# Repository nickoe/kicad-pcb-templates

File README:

This is just some random PCB templates for Kicad.

RasPi-BplusHAT.kicad_pcb is imported from an Eagle pcb and fixed.
Taken from
http://www.raspberrypi.org/forums/viewtopic.php?f=100&t=82618

RasPi-BplusHAT-directimport.kicad_pcb is just the board saved directly
after importing it in Kicad.

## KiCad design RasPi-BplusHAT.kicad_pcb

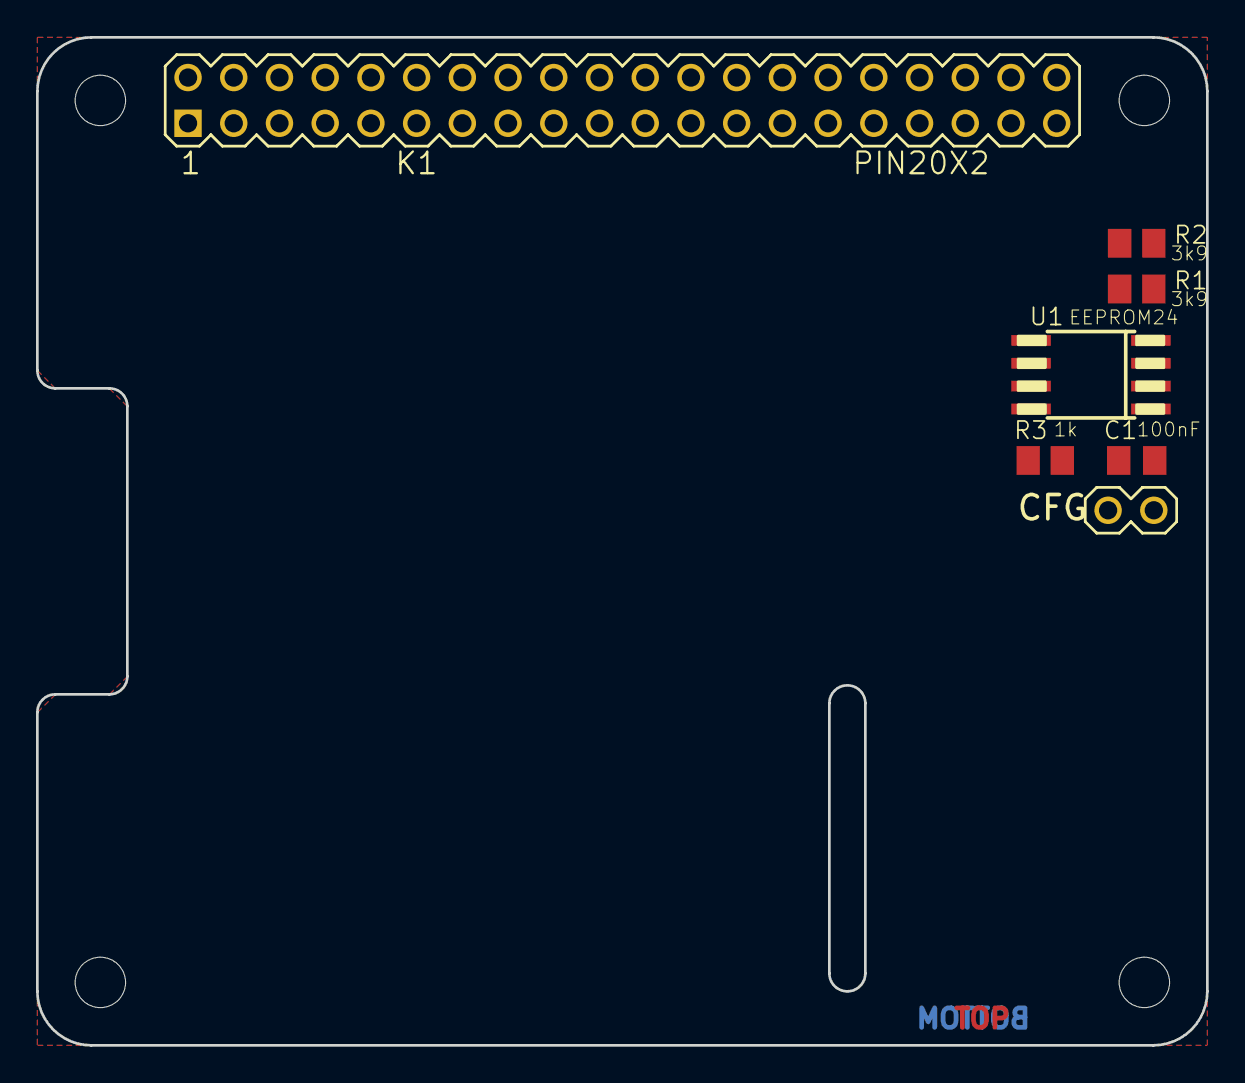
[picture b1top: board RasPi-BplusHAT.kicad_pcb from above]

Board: 2 copper layers, 65.0 x 56.0 mm, 11 parts (0 on the bottom side), 6 nets, no tracks yet.

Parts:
@HOLE0, @HOLE1, @HOLE2, @HOLE3: (no value)
C1: 100nF; C0805K
CFG: PIN_W_2
K1: PIN20X2; PIN_20X2
R1, R2: 3k9; M0805
R3: 1k; M0805
U1: EEPROM24; SOIC8

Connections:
+3V3: C1.1, K1.1, K1.17, R1.2, R2.2, R3.2, U1.8
+5V: K1.2, K1.4
GND: C1.2, CFG.2, K1.6, K1.9, K1.14, K1.20, K1.25, K1.30, K1.34, K1.39, U1.1, U1.2, U1.3, U1.4
unnamed: K1.28, R1.1, U1.6
unnamed: K1.27, R2.1, U1.5
unnamed: CFG.1, R3.1, U1.7

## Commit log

2014-09-13 Addinf Raspberry Pi B+ HAT
2014-09-13 Fix typo
2014-09-13 Fix zones
2014-09-13 Add RasPi Bplus with camera slot
2014-09-13 Update cam slot arc
2014-09-13 Adding the Intel Edison module footprint
